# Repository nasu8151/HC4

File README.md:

¡¡¡ガバガバEnglish注意報発令中!!!

# Table of Contents
- [Table of Contents](#table-of-contents)
- [Descriptions](#descriptions)
- [Architecture](#architecture)
  - [Overview](#overview)
  - [Block diagram](#block-diagram)
  - [Instructions list](#instructions-list)
- [Software](#software)
- [List of files and folders](#list-of-files-and-folders)

# Descriptions

A 4- or 8-bit CPU made with 74-series logic ICs.

# Manuals

- Hardware manual (JP): [UsersManual_Hardware.md](./UsersManual_Hardware.md)
- Software manual (EN): [UsersManual_Software.md](./UsersManual_Software.md)
- Software manual (JP): [UsersManual_Software_JP.md](./UsersManual_Software_JP.md)

Document roles:

- Hardware manual (JP): block-level architecture, buses, control signals, model differences.
- Software manual (EN/JP): instruction set reference, programming caveats, and LED blink tutorial.

# Architecture
## Overview

HC4 has an 8-bit wide address bus and a 4-bit wide data bus.
All of instructions are 8-bit wide.

## Block diagram

## Instructions list

Please refer to [here](https://github.com/nasu8151/HC4/blob/main/UsersManual_Software.md).

## Schematics and Boards

If you don't have [KiCAD](https://www.kicad.org/), you can use KiCanvas to see our schematics and boards.
* [HC4](https://kicanvas.org/?repo=https%3A%2F%2Fgithub.com%2Fnasu8151%2FHC4%2Ftree%2Fmain%2FHC4_KiCad)
* [HC4<sub>E</sub>](https://kicanvas.org/?repo=https%3A%2F%2Fgithub.com%2Fnasu8151%2FHC4%2Ftree%2Fmain%2FHC4_KiCad_EE)

# Software

## Assembler

The assembler for this CPU can be found [here](https://github.com/nasu8151/hcxasm).
Please see the documents for syntax and other details.

## HC4eROMandRAM

This is a ROM/RAM emulator for HC4<sub>E</sub>.

# List of files and folders

<pre>
.
├─extra
├─HC4eROMandRAM
│  └─inst
├─hc4_asm
│  └─src
│      └─debug_data
├─HC4_KiCad
│  ├─HC4_gbr
│  ├─Library.pretty
│  └─sim
├─HC4_KiCad_EE
│  ├─HC4_KiCad_EE-backups
│  ├─Library.pretty
│  └─production
├─HC_MemoryBoard
│  ├─production
│  └─ThroughHole.pretty
└─verilog
    ├─HC4
    ├─HC4e
    └─HC8
</pre>

* [README.md](https://github.com/nasu8151/HC4) : This file.
* [UsersManual_Software.md](https://github.com/nasu8151/HC4/blob/main/UsersManual_Software.md) : Instruction manual.
* [hc4_asm/](https://github.com/nasu8151/HC4/blob/main/hc4_asm) : [DEPRECATED] : [Use new assembler](https://github.com/nasu8151/hcxasm). An assembler for the HC4 CPU.
* [HC4_KiCad](https://github.com/nasu8151/HC4/blob/main/HC4_KiCad) : Schematics and a board of the HC4.
* [HC4_KiCad_EE](https://github.com/nasu8151/HC4/blob/main/HC4_KiCad_EE) : Schematics and a board of the HC4<sub>E</sub> (Used to be called "HC4 Education Edition").
* [HC_MemoryBoard](https://github.com/nasu8151/HC4/blob/main/HC4_KiCad_EE) : A schematic and a board for SRAM and I/O.
* verilog/
  * [verilog/HC4](https://github.com/nasu8151/HC4/blob/main/verilog/HC4) : Verilog simulation files of the HC4 CPU.
  * [verilog/HC8](https://github.com/nasu8151/blob/main/HC4/verilog/HC8) : Verilog simulation files of the HC8 CPU.
  * [verilog/HC4e](https://github.com/nasu8151/blob/main/HC4/verilog/HC8) : Verilog simulation files of the HC4e CPU.

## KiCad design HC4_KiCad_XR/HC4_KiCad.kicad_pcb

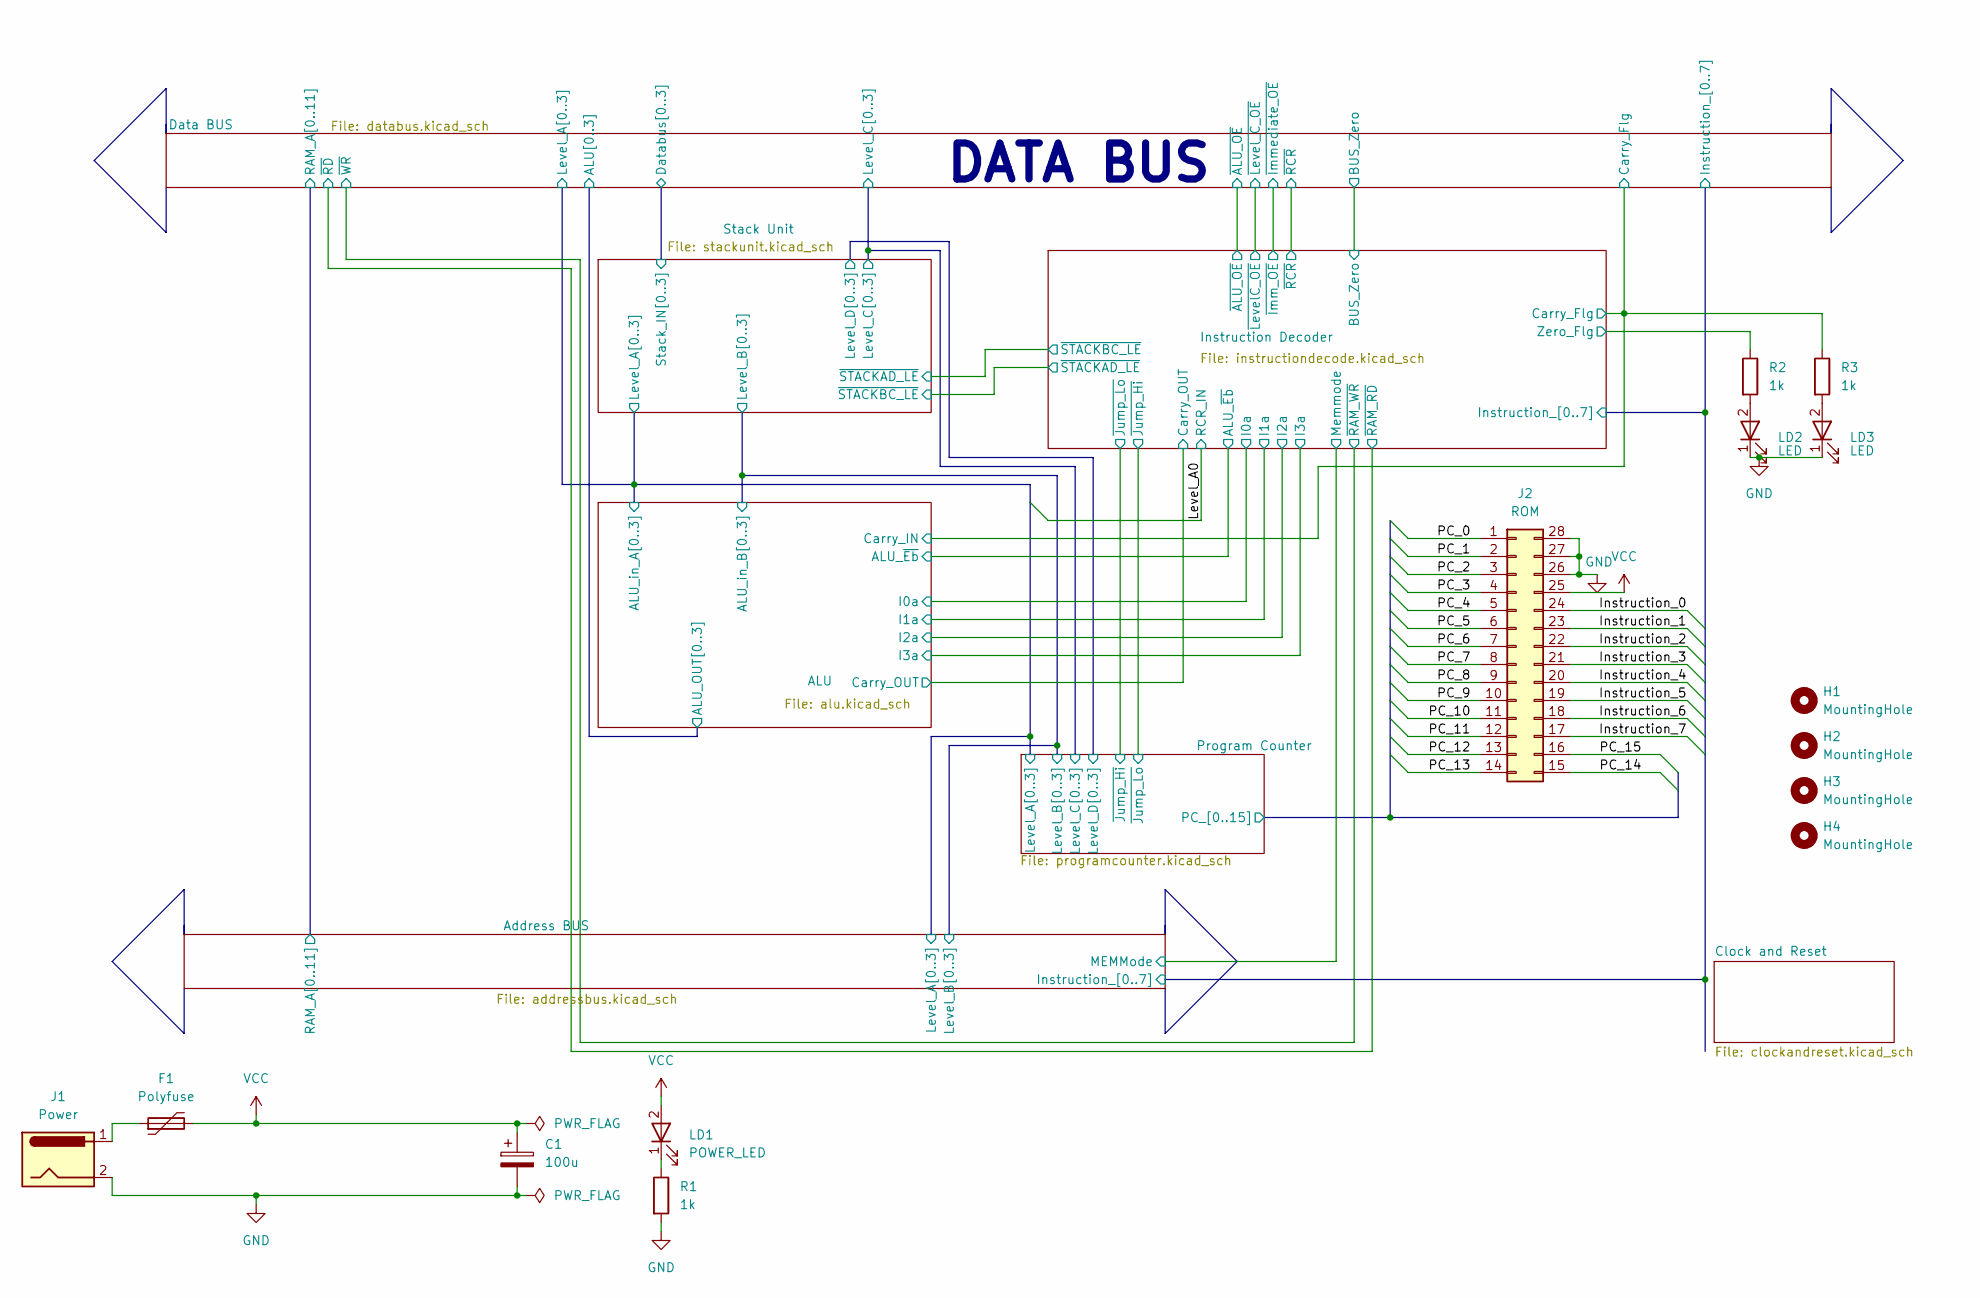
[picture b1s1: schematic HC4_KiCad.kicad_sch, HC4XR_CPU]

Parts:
C1: 100u; CP_Radial_D5.0mm_P2.50mm
F1: Polyfuse; Fuse_Bourns_MF-RG400
H1, H2, H3, H4: MountingHole; MountingHole_3.2mm_M3
J1: Power; BarrelJack_GCT_DCJ200-10-A_Horizontal
J2: ROM; PinHeader_2x14_P2.54mm_Vertical
LD1: POWER_LED; LED_Rectangular_W5.0mm_H2.0mm
LD2, LD3: LED; LED_Rectangular_W5.0mm_H2.0mm
R1, R2, R3: 1k; R_0603_1608Metric

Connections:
/Address BUS/Instruction_0: J2.24; also elsewhere on the board
/Address BUS/Instruction_1: J2.23; also elsewhere on the board
/Address BUS/Instruction_2: J2.22; also elsewhere on the board
/Address BUS/Instruction_3: J2.21; also elsewhere on the board
/Address BUS/Instruction_4: J2.20; also elsewhere on the board
/Address BUS/Instruction_5: J2.19; also elsewhere on the board
/Address BUS/Instruction_6: J2.18; also elsewhere on the board
/Address BUS/Instruction_7: J2.17; also elsewhere on the board
/Instruction Decoder/Carry_Flg: R3.1; also elsewhere on the board
/Instruction Decoder/Zero_Flg: R2.1; also elsewhere on the board
/Program Counter/PC_0: J2.1; also elsewhere on the board
/Program Counter/PC_1: J2.2; also elsewhere on the board
/Program Counter/PC_2: J2.3; also elsewhere on the board
/Program Counter/PC_3: J2.4; also elsewhere on the board
/Program Counter/PC_4: J2.5; also elsewhere on the board
/Program Counter/PC_5: J2.6; also elsewhere on the board
/Program Counter/PC_6: J2.7; also elsewhere on the board
/Program Counter/PC_7: J2.8; also elsewhere on the board
/Program Counter/PC_8: J2.9; also elsewhere on the board
/Program Counter/PC_9: J2.10; also elsewhere on the board
/Program Counter/PC_10: J2.11; also elsewhere on the board
/Program Counter/PC_11: J2.12; also elsewhere on the board
/Program Counter/PC_12: J2.13; also elsewhere on the board
/Program Counter/PC_13: J2.14; also elsewhere on the board
/Program Counter/PC_14: J2.15; also elsewhere on the board
/Program Counter/PC_15: J2.16; also elsewhere on the board
GND: C1.2, J1.2, J2.26, J2.27, J2.28, LD2.1 (K_1), LD3.1 (K_1), R1.2; also elsewhere on the board
unnamed: F1.1, J1.1
unnamed: LD1.1 (K_1), R1.1
unnamed: LD2.2, R2.2
unnamed: LD3.2, R3.2
VCC: C1.1, F1.2, J2.25, LD1.2; also elsewhere on the board

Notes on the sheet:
DATA BUS

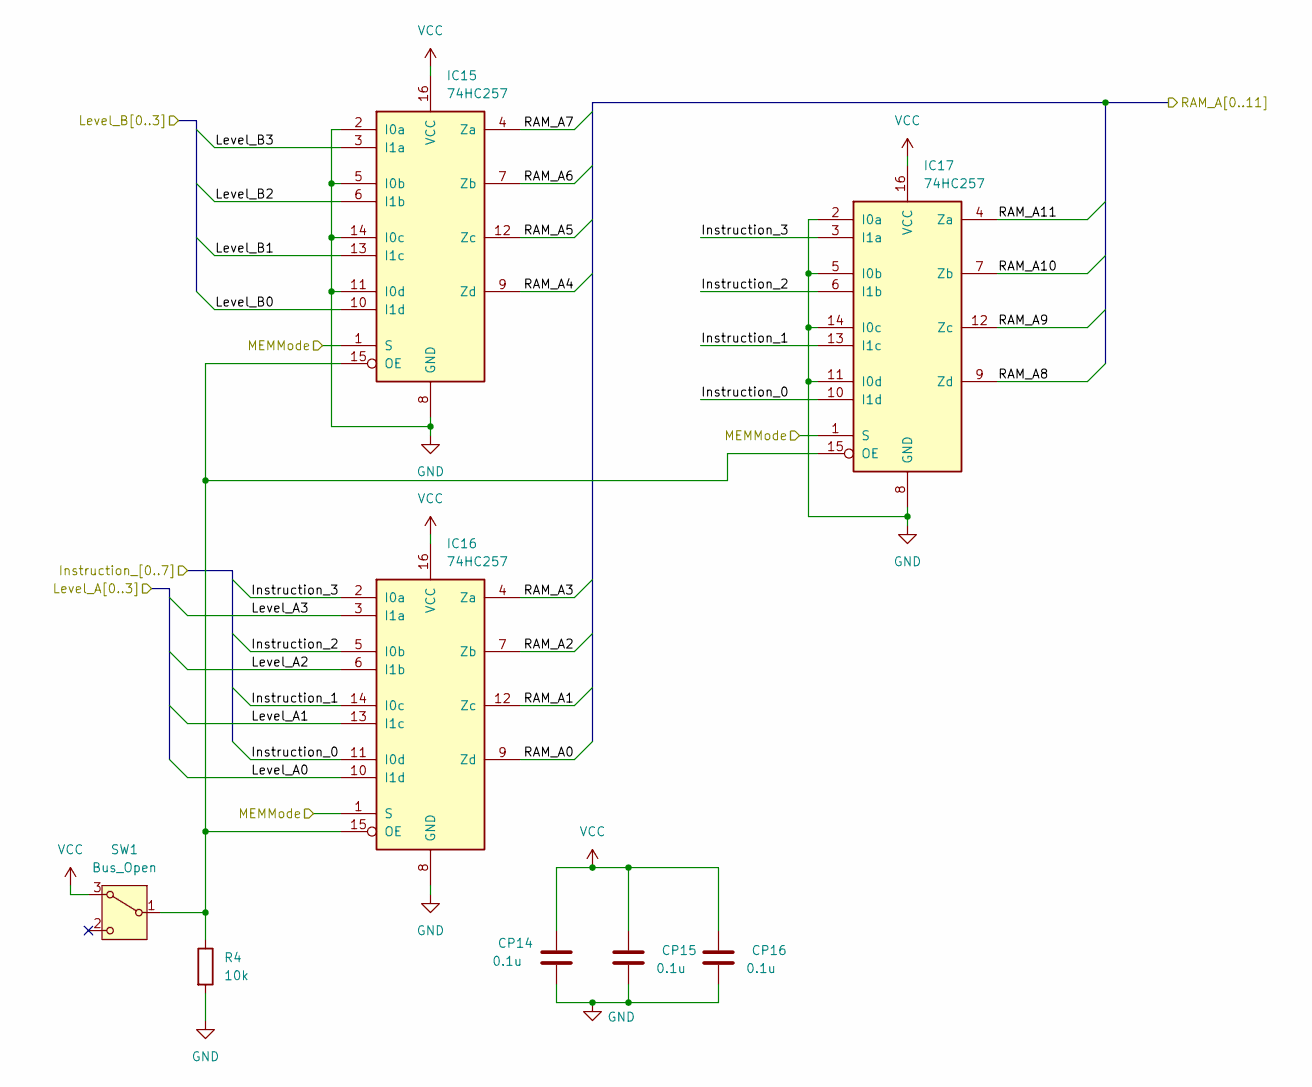
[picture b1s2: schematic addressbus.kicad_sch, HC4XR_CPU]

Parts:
CP14, CP15, CP16: 0.1u; C_0603_1608Metric
IC15, IC16, IC17: 74HC257; DIP-16_W7.62mm
R4: 10k; R_0603_1608Metric
SW1: Bus_Open; SW_Slide-03_Wuerth-WS-SLTV_10x2.5x6.4_P2.54mm

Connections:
/ALU/ALU_in_A0: IC16.10 (I1d); also elsewhere on the board
/ALU/ALU_in_A1: IC16.13 (I1c); also elsewhere on the board
/ALU/ALU_in_A2: IC16.6 (I1b); also elsewhere on the board
/ALU/ALU_in_A3: IC16.3 (I1a); also elsewhere on the board
/ALU/ALU_in_B0: IC15.10 (I1d); also elsewhere on the board
/ALU/ALU_in_B1: IC15.13 (I1c); also elsewhere on the board
/ALU/ALU_in_B2: IC15.6 (I1b); also elsewhere on the board
/ALU/ALU_in_B3: IC15.3 (I1a); also elsewhere on the board
/Address BUS/Instruction_0: IC16.11 (I0d), IC17.10 (I1d); also elsewhere on the board
/Address BUS/Instruction_1: IC16.14 (I0c), IC17.13 (I1c); also elsewhere on the board
/Address BUS/Instruction_2: IC16.5 (I0b), IC17.6 (I1b); also elsewhere on the board
/Address BUS/Instruction_3: IC16.2 (I0a), IC17.3 (I1a); also elsewhere on the board
/Address BUS/MEMMode: IC15.1 (S), IC16.1 (S), IC17.1 (S); also elsewhere on the board
/Address BUS/RAM_A0: IC16.9 (Zd); also elsewhere on the board
/Address BUS/RAM_A1: IC16.12 (Zc); also elsewhere on the board
/Address BUS/RAM_A2: IC16.7 (Zb); also elsewhere on the board
/Address BUS/RAM_A3: IC16.4 (Za); also elsewhere on the board
/Address BUS/RAM_A4: IC15.9 (Zd); also elsewhere on the board
/Address BUS/RAM_A5: IC15.12 (Zc); also elsewhere on the board
/Address BUS/RAM_A6: IC15.7 (Zb); also elsewhere on the board
/Address BUS/RAM_A7: IC15.4 (Za); also elsewhere on the board
/Address BUS/RAM_A8: IC17.9 (Zd); also elsewhere on the board
/Address BUS/RAM_A9: IC17.12 (Zc); also elsewhere on the board
/Address BUS/RAM_A10: IC17.7 (Zb); also elsewhere on the board
/Address BUS/RAM_A11: IC17.4 (Za); also elsewhere on the board
GND: CP14.2, CP15.2, CP16.2, IC15.2 (I0a), IC15.5 (I0b), IC15.8 (GND), IC15.11 (I0d), IC15.14 (I0c), IC16.8 (GND), IC17.2 (I0a), IC17.5 (I0b), IC17.8 (GND), IC17.11 (I0d), IC17.14 (I0c), R4.2; also elsewhere on the board
unnamed: IC15.15 (OE), IC16.15 (OE), IC17.15 (OE), R4.1, SW1.1 (B)
VCC: CP14.1, CP15.1, CP16.1, IC15.16 (VCC), IC16.16 (VCC), IC17.16 (VCC), SW1.3 (A); also elsewhere on the board

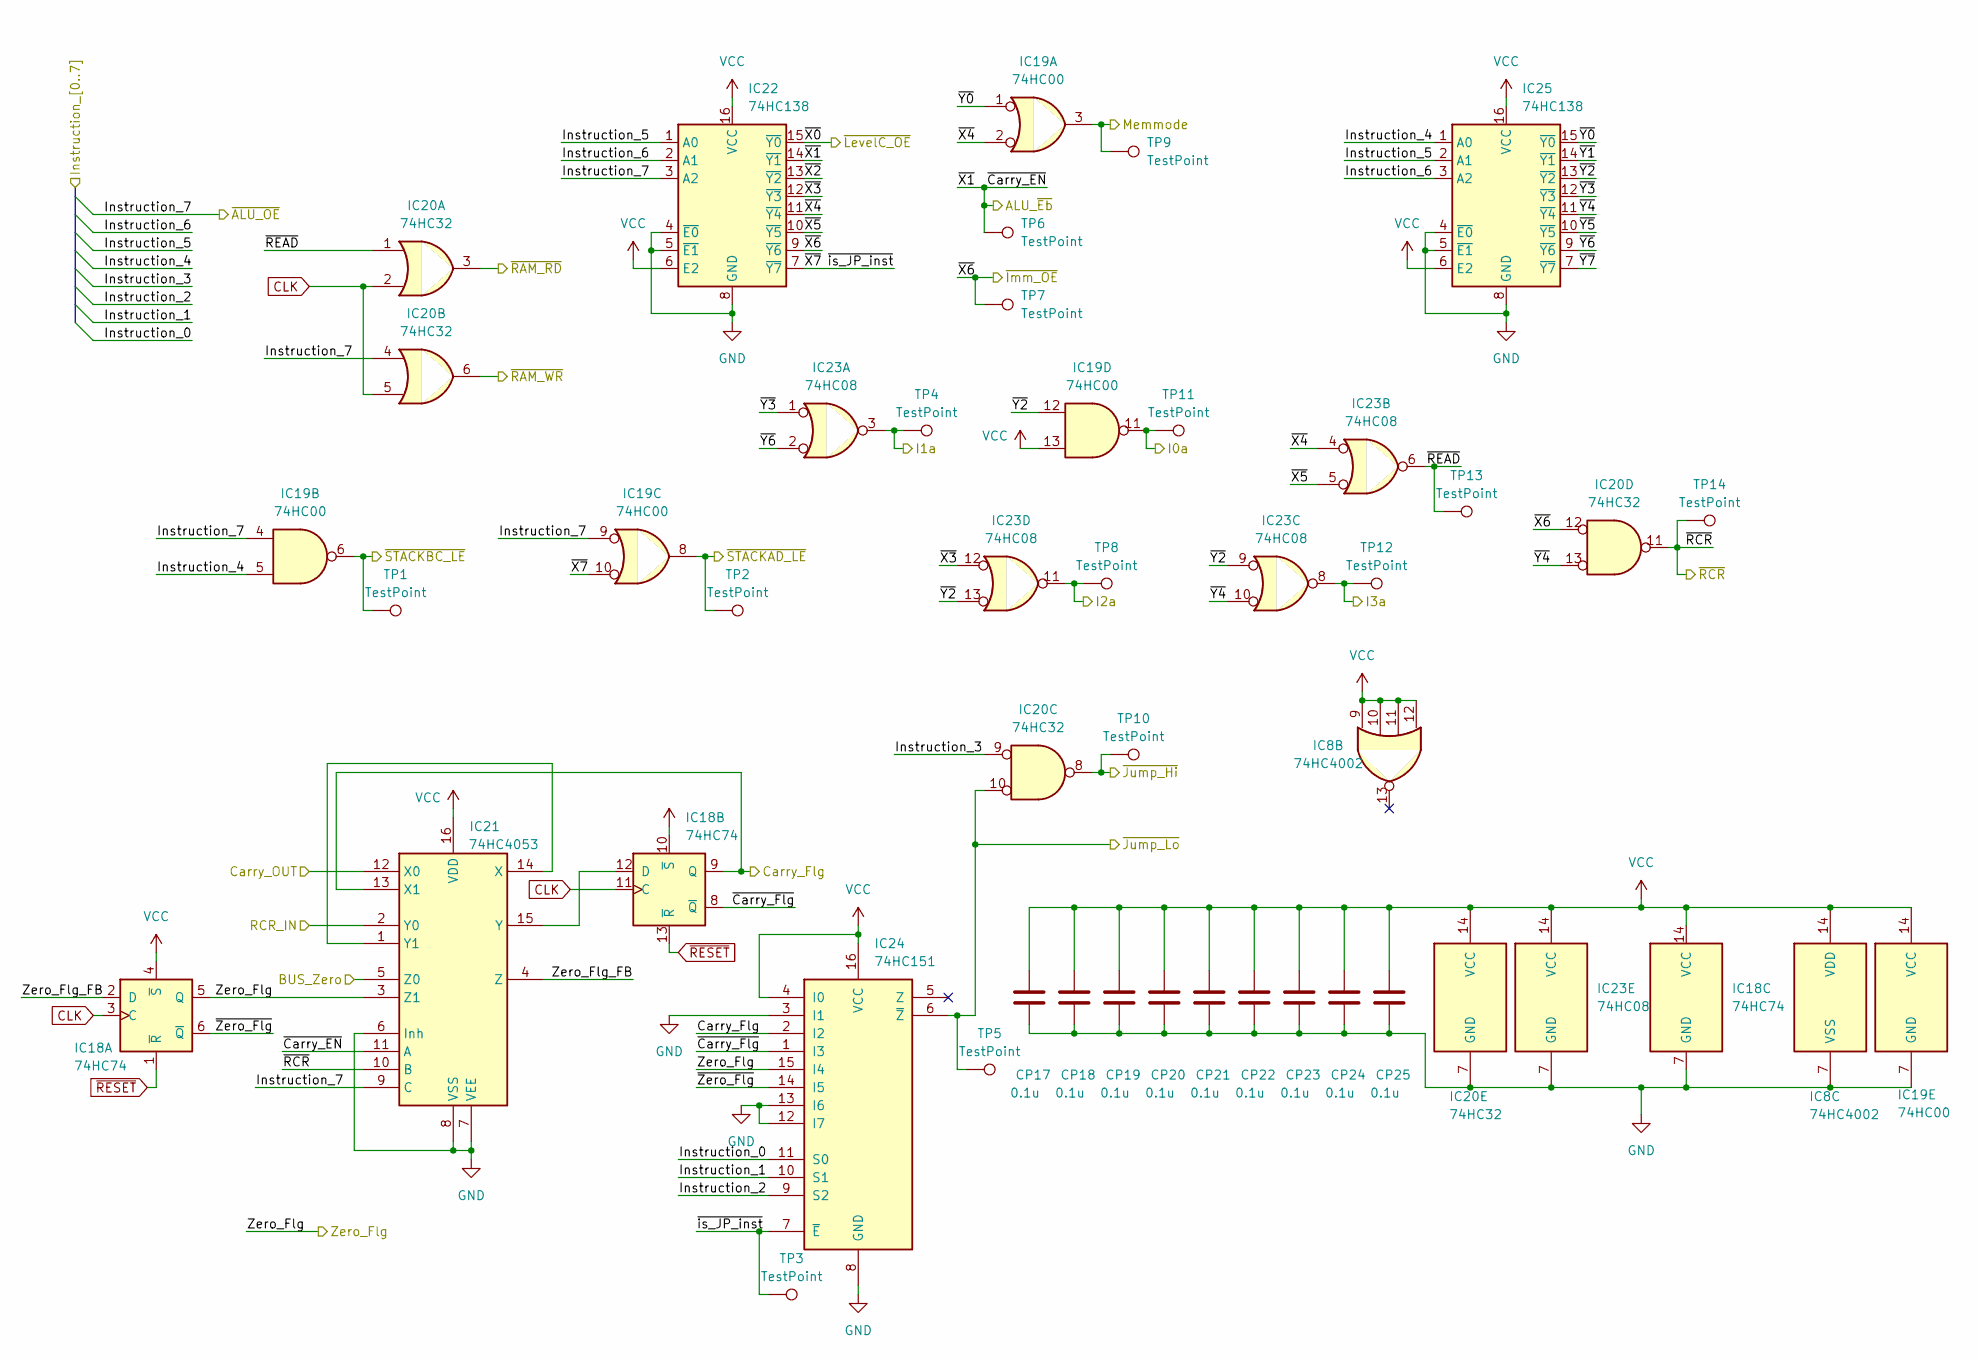
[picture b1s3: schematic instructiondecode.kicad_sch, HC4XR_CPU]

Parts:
CP17, CP18, CP19, CP20, CP21, CP22, CP23, CP24, CP25: 0.1u; C_0603_1608Metric
IC8: 74HC4002; DIP-14_W7.62mm
IC18: 74HC74; DIP-14_W7.62mm
IC19: 74HC00; DIP-14_W7.62mm
IC20: 74HC32; DIP-14_W7.62mm
IC21: 74HC4053; DIP-16_W7.62mm
IC22, IC25: 74HC138; DIP-16_W7.62mm
IC23: 74HC08; DIP-14_W7.62mm
IC24: 74HC151; DIP-16_W7.62mm
TP1, TP2, TP3, TP4, TP5, TP6, TP7, TP8, TP9, TP10, TP11, TP12, TP13, TP14: TestPoint; TestPoint_THTPad_1.0x1.0mm_Drill0.5mm

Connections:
/ALU/ALU_in_A0: IC21.2 (Y0); also elsewhere on the board
/ALU/Carry_OUT: IC21.12 (X0); also elsewhere on the board
/ALU/I0a: IC19.11, TP11.1 (1_1); also elsewhere on the board
/ALU/I1a: IC23.3, TP4.1 (1_1); also elsewhere on the board
/ALU/I2a: IC23.11, TP8.1 (1_1); also elsewhere on the board
/ALU/I3a: IC23.8, TP12.1 (1_1); also elsewhere on the board
/Address BUS/Instruction_0: IC24.11 (S0); also elsewhere on the board
/Address BUS/Instruction_1: IC24.10 (S1); also elsewhere on the board
/Address BUS/Instruction_2: IC24.9 (S2); also elsewhere on the board
/Address BUS/Instruction_3: IC20.9; also elsewhere on the board
/Address BUS/Instruction_4: IC19.5, IC25.1 (A0); also elsewhere on the board
/Address BUS/Instruction_5: IC22.1 (A0), IC25.2 (A1); also elsewhere on the board
/Address BUS/Instruction_6: IC22.2 (A1), IC25.3 (A2); also elsewhere on the board
/Address BUS/Instruction_7: IC19.4, IC19.9, IC20.4, IC21.9 (C), IC22.3 (A2); also elsewhere on the board
/Address BUS/MEMMode: IC19.3, TP9.1 (1_1); also elsewhere on the board
/Data BUS/BUS_Zero: IC8.1, IC21.5 (Z0)
/Data BUS/Databus0: IC8.5; also elsewhere on the board
/Data BUS/Databus1: IC8.4; also elsewhere on the board
/Data BUS/Databus2: IC8.3; also elsewhere on the board
/Data BUS/Databus3: IC8.2; also elsewhere on the board
/Data BUS/~RD: IC20.3; also elsewhere on the board
/Data BUS/~WR: IC20.6; also elsewhere on the board
/Instruction Decoder/Carry_Flg: IC18.9 (Q), IC21.13 (X1), IC24.2 (I2); also elsewhere on the board
/Instruction Decoder/Zero_Flg: IC18.5 (Q), IC21.3 (Z1), IC24.15 (I4); also elsewhere on the board
/Instruction Decoder/Zero_Flg_FB: IC18.2 (D), IC21.4 (Z)
/Instruction Decoder/~Carry_EN: IC21.11 (A), IC22.14 (~Y1), TP6.1 (1_1); also elsewhere on the board
/Instruction Decoder/~Carry_Flg: IC18.8 (~Q), IC24.1 (I3)
/Instruction Decoder/~Jump_Hi: IC20.8, TP10.1 (1_1); also elsewhere on the board
/Instruction Decoder/~Jump_Lo: IC20.10, IC24.6 (~Z), TP5.1 (1_1); also elsewhere on the board
/Instruction Decoder/~RCR: IC20.11, IC21.10 (B), TP14.1 (1_1); also elsewhere on the board
/Instruction Decoder/~READ: IC20.1, IC23.6, TP13.1 (1_1)
/Instruction Decoder/~STACKAD_LE: IC19.8, TP2.1 (1_1); also elsewhere on the board
/Instruction Decoder/~STACKBC_LE: IC19.6, TP1.1 (1_1); also elsewhere on the board
/Instruction Decoder/~X0: IC22.15 (~Y0); also elsewhere on the board
/Instruction Decoder/~X2: IC22.13 (~Y2)
/Instruction Decoder/~X3: IC22.12 (~Y3), IC23.12
/Instruction Decoder/~X4: IC19.2, IC22.11 (~Y4), IC23.4
/Instruction Decoder/~X5: IC22.10 (~Y5), IC23.5
/Instruction Decoder/~X6: IC20.12, IC22.9 (~Y6), TP7.1 (1_1); also elsewhere on the board
/Instruction Decoder/~X7: IC19.10, IC22.7 (~Y7), IC24.7 (~E), TP3.1 (1_1)
/Instruction Decoder/~Y0: IC19.1, IC25.15 (~Y0)
/Instruction Decoder/~Y1: IC25.14 (~Y1)
/Instruction Decoder/~Y2: IC19.12, IC23.9, IC23.13, IC25.13 (~Y2)
/Instruction Decoder/~Y3: IC23.1, IC25.12 (~Y3)
/Instruction Decoder/~Y4: IC20.13, IC23.10, IC25.11 (~Y4)
/Instruction Decoder/~Y5: IC25.10 (~Y5)
/Instruction Decoder/~Y6: IC23.2, IC25.9 (~Y6)
/Instruction Decoder/~Y7: IC25.7 (~Y7)
/Instruction Decoder/~Zero_Flg: IC18.6 (~Q), IC24.14 (I5)
CLK: IC18.3 (C), IC18.11 (C), IC20.2, IC20.5; also elsewhere on the board
GND: CP17.2, CP18.2, CP19.2, CP20.2, CP21.2, CP22.2, CP23.2, CP24.2, CP25.2, IC8.7 (VSS), IC18.7 (GND), IC19.7 (GND), IC20.7 (GND), IC21.6 (Inh), IC21.7 (VEE), IC21.8 (VSS), IC22.4 (~E0), IC22.5 (~E1), IC22.8 (GND), IC23.7 (GND), IC24.3 (I1), IC24.8 (GND), IC24.12 (I7), IC24.13 (I6), IC25.4 (~E0), IC25.5 (~E1), IC25.8 (GND); also elsewhere on the board
unnamed: IC18.12 (D), IC21.15 (Y)
unnamed: IC21.1 (Y1), IC21.14 (X)
VCC: CP17.1, CP18.1, CP19.1, CP20.1, CP21.1, CP22.1, CP23.1, CP24.1, CP25.1, IC8.9, IC8.10, IC8.11, IC8.12, IC8.14 (VDD), IC18.4 (~S), IC18.10 (~S), IC18.14 (VCC), IC19.13, IC19.14 (VCC), IC20.14 (VCC), IC21.16 (VDD), IC22.6 (E2), IC22.16 (VCC), IC23.14 (VCC), IC24.4 (I0), IC24.16 (VCC), IC25.6 (E2), IC25.16 (VCC); also elsewhere on the board
~RESET: IC18.1 (~R), IC18.13 (~R); also elsewhere on the board

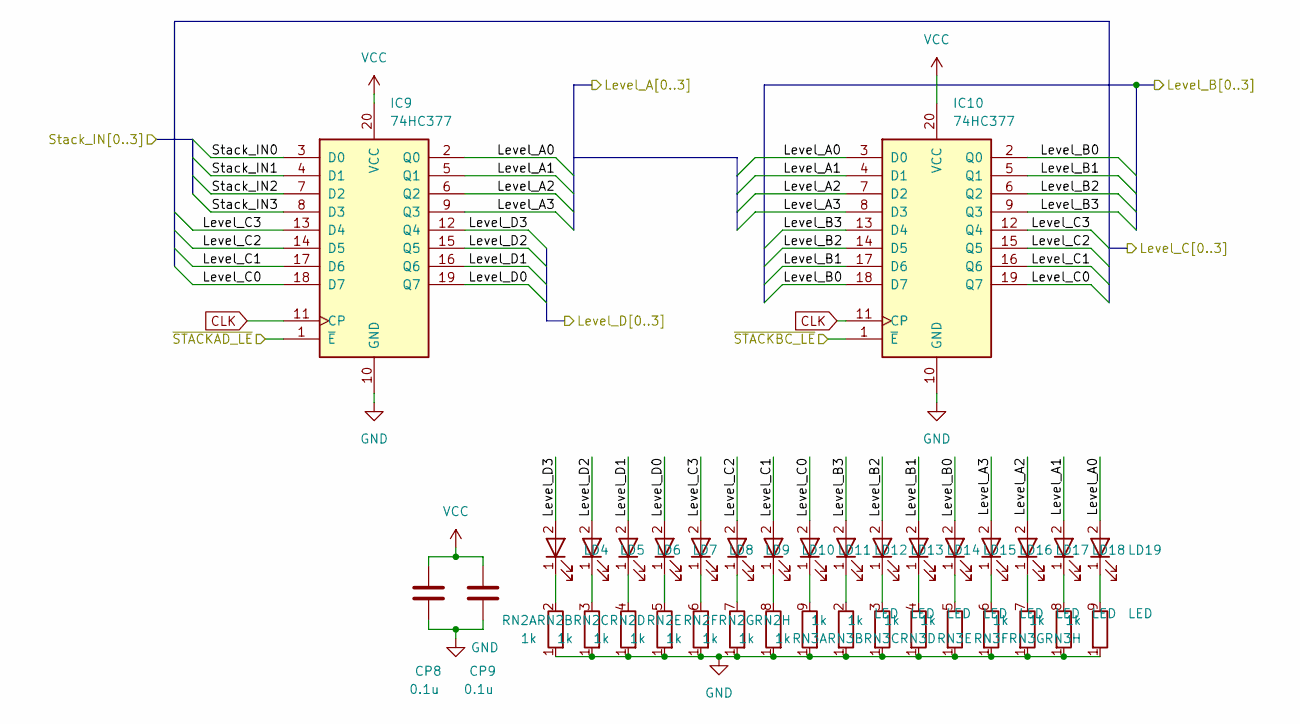
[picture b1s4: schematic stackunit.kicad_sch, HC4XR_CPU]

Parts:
CP8, CP9: 0.1u; C_0603_1608Metric
IC9, IC10: 74HC377; DIP-20_W7.62mm
LD4, LD5, LD6, LD7, LD8, LD9, LD10, LD11, LD12, LD13, LD14, LD15, LD16, LD17, LD18, LD19: LED; LED_Rectangular_W5.0mm_H2.0mm
RN2, RN3: 1k; R_Array_SIP9

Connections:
/ALU/ALU_in_A0: IC9.2 (Q0), IC10.3 (D0), LD19.2; also elsewhere on the board
/ALU/ALU_in_A1: IC9.5 (Q1), IC10.4 (D1), LD18.2; also elsewhere on the board
/ALU/ALU_in_A2: IC9.6 (Q2), IC10.7 (D2), LD17.2; also elsewhere on the board
/ALU/ALU_in_A3: IC9.9 (Q3), IC10.8 (D3), LD16.2; also elsewhere on the board
/ALU/ALU_in_B0: IC10.2 (Q0), IC10.18 (D7), LD15.2; also elsewhere on the board
/ALU/ALU_in_B1: IC10.5 (Q1), IC10.17 (D6), LD14.2; also elsewhere on the board
/ALU/ALU_in_B2: IC10.6 (Q2), IC10.14 (D5), LD13.2; also elsewhere on the board
/ALU/ALU_in_B3: IC10.9 (Q3), IC10.13 (D4), LD12.2; also elsewhere on the board
/Data BUS/Databus0: IC9.3 (D0); also elsewhere on the board
/Data BUS/Databus1: IC9.4 (D1); also elsewhere on the board
/Data BUS/Databus2: IC9.7 (D2); also elsewhere on the board
/Data BUS/Databus3: IC9.8 (D3); also elsewhere on the board
/Data BUS/Level_C0: IC9.18 (D7), IC10.19 (Q7), LD11.2; also elsewhere on the board
/Data BUS/Level_C1: IC9.17 (D6), IC10.16 (Q6), LD10.2; also elsewhere on the board
/Data BUS/Level_C2: IC9.14 (D5), IC10.15 (Q5), LD9.2; also elsewhere on the board
/Data BUS/Level_C3: IC9.13 (D4), IC10.12 (Q4), LD8.2; also elsewhere on the board
/Instruction Decoder/~STACKAD_LE: IC10.1 (~E); also elsewhere on the board
/Instruction Decoder/~STACKBC_LE: IC9.1 (~E); also elsewhere on the board
/Program Counter/Level_D0: IC9.19 (Q7), LD7.2; also elsewhere on the board
/Program Counter/Level_D1: IC9.16 (Q6), LD6.2; also elsewhere on the board
/Program Counter/Level_D2: IC9.15 (Q5), LD5.2; also elsewhere on the board
/Program Counter/Level_D3: IC9.12 (Q4), LD4.2; also elsewhere on the board
CLK: IC9.11 (CP), IC10.11 (CP); also elsewhere on the board
GND: CP8.2, CP9.2, IC9.10 (GND), IC10.10 (GND), RN2.1 (R1), RN3.1 (R1); also elsewhere on the board
unnamed: LD4.1 (K_1), RN2.2 (R1.2)
unnamed: LD5.1 (K_1), RN2.3 (R2.2)
unnamed: LD6.1 (K_1), RN2.4 (R3.2)
unnamed: LD7.1 (K_1), RN2.5 (R4.2)
unnamed: LD8.1 (K_1), RN2.6 (R5.2)
unnamed: LD9.1 (K_1), RN2.7 (R6.2)
unnamed: LD10.1 (K_1), RN2.8 (R7.2)
unnamed: LD11.1 (K_1), RN2.9 (R8.2)
unnamed: LD12.1 (K_1), RN3.2 (R1.2)
unnamed: LD13.1 (K_1), RN3.3 (R2.2)
unnamed: LD14.1 (K_1), RN3.4 (R3.2)
unnamed: LD15.1 (K_1), RN3.5 (R4.2)
unnamed: LD16.1 (K_1), RN3.6 (R5.2)
unnamed: LD17.1 (K_1), RN3.7 (R6.2)
unnamed: LD18.1 (K_1), RN3.8 (R7.2)
unnamed: LD19.1 (K_1), RN3.9 (R8.2)
VCC: CP8.1, CP9.1, IC9.20 (VCC), IC10.20 (VCC); also elsewhere on the board

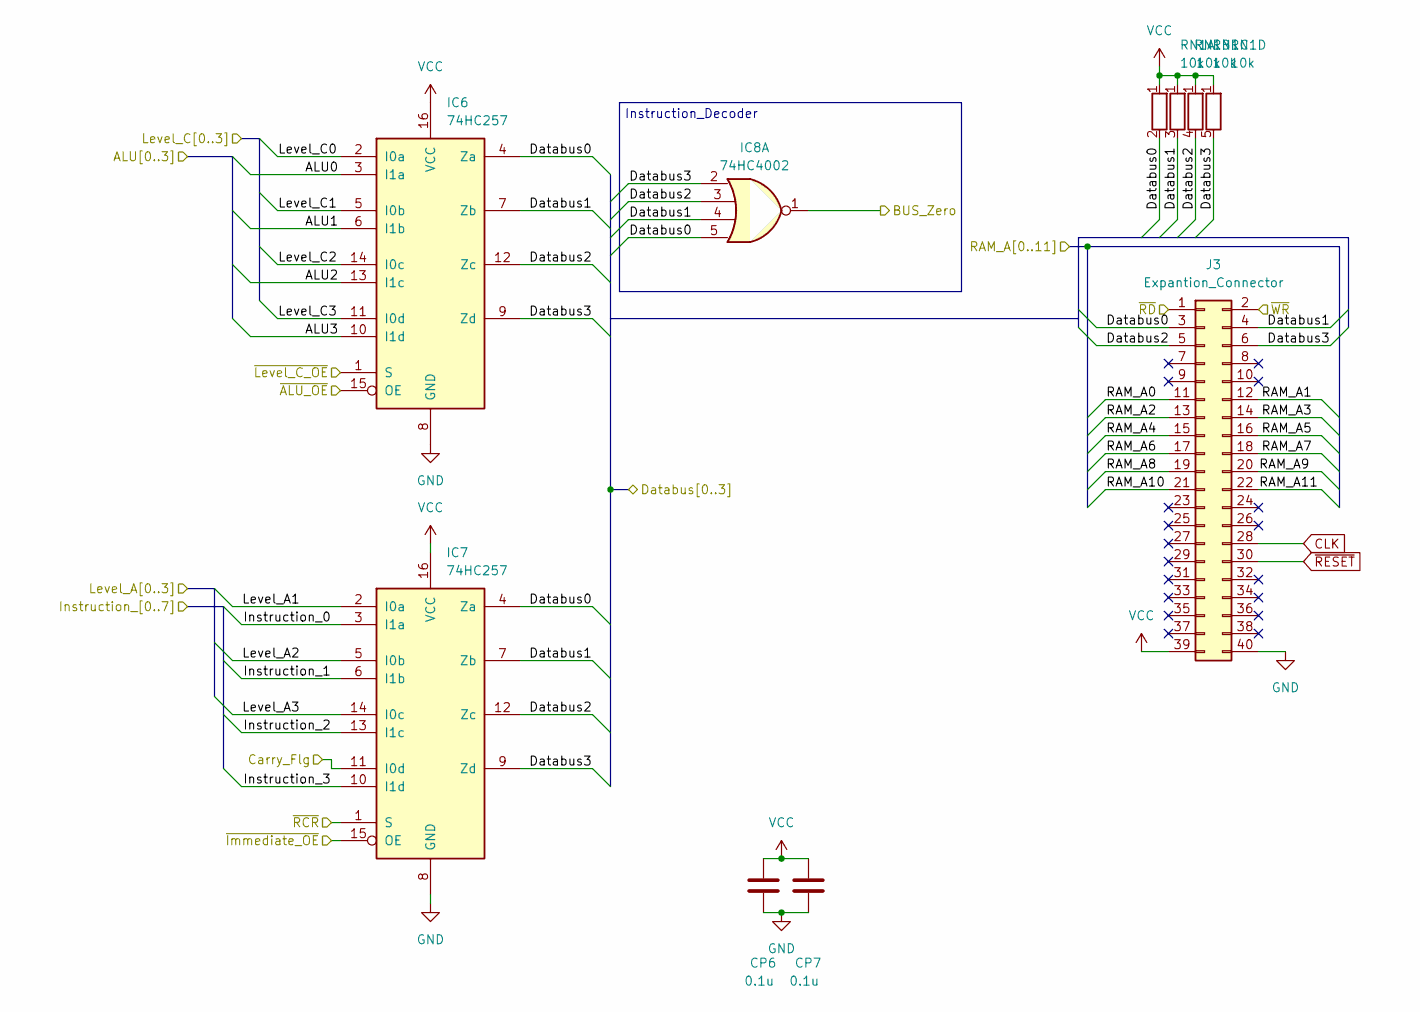
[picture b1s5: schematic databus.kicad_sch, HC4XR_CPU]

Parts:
CP6, CP7: 0.1u; C_0603_1608Metric
IC6, IC7: 74HC257; DIP-16_W7.62mm
IC8: 74HC4002; DIP-14_W7.62mm
J3: Expantion_Connector; PinHeader_2x20_P2.54mm_Vertical
RN1: 10k; R_Array_SIP5

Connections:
/ALU/ALU_OUT0: IC6.3 (I1a); also elsewhere on the board
/ALU/ALU_OUT1: IC6.6 (I1b); also elsewhere on the board
/ALU/ALU_OUT2: IC6.13 (I1c); also elsewhere on the board
/ALU/ALU_OUT3: IC6.10 (I1d); also elsewhere on the board
/ALU/ALU_in_A1: IC7.2 (I0a); also elsewhere on the board
/ALU/ALU_in_A2: IC7.5 (I0b); also elsewhere on the board
/ALU/ALU_in_A3: IC7.14 (I0c); also elsewhere on the board
/Address BUS/Instruction_0: IC7.3 (I1a); also elsewhere on the board
/Address BUS/Instruction_1: IC7.6 (I1b); also elsewhere on the board
/Address BUS/Instruction_2: IC7.13 (I1c); also elsewhere on the board
/Address BUS/Instruction_3: IC7.10 (I1d); also elsewhere on the board
/Address BUS/Instruction_7: IC6.15 (OE); also elsewhere on the board
/Address BUS/RAM_A0: J3.11; also elsewhere on the board
/Address BUS/RAM_A1: J3.12; also elsewhere on the board
/Address BUS/RAM_A2: J3.13; also elsewhere on the board
/Address BUS/RAM_A3: J3.14; also elsewhere on the board
/Address BUS/RAM_A4: J3.15; also elsewhere on the board
/Address BUS/RAM_A5: J3.16; also elsewhere on the board
/Address BUS/RAM_A6: J3.17; also elsewhere on the board
/Address BUS/RAM_A7: J3.18; also elsewhere on the board
/Address BUS/RAM_A8: J3.19; also elsewhere on the board
/Address BUS/RAM_A9: J3.20; also elsewhere on the board
/Address BUS/RAM_A10: J3.21; also elsewhere on the board
/Address BUS/RAM_A11: J3.22; also elsewhere on the board
/Data BUS/BUS_Zero: IC8.1; also elsewhere on the board
/Data BUS/Databus0: IC6.4 (Za), IC7.4 (Za), IC8.5, J3.3, RN1.2 (R1.2); also elsewhere on the board
/Data BUS/Databus1: IC6.7 (Zb), IC7.7 (Zb), IC8.4, J3.4, RN1.3 (R2.2); also elsewhere on the board
/Data BUS/Databus2: IC6.12 (Zc), IC7.12 (Zc), IC8.3, J3.5, RN1.4 (R3.2); also elsewhere on the board
/Data BUS/Databus3: IC6.9 (Zd), IC7.9 (Zd), IC8.2, J3.6, RN1.5 (R4.2); also elsewhere on the board
/Data BUS/Level_C0: IC6.2 (I0a); also elsewhere on the board
/Data BUS/Level_C1: IC6.5 (I0b); also elsewhere on the board
/Data BUS/Level_C2: IC6.14 (I0c); also elsewhere on the board
/Data BUS/Level_C3: IC6.11 (I0d); also elsewhere on the board
/Data BUS/~RD: J3.1; also elsewhere on the board
/Data BUS/~WR: J3.2; also elsewhere on the board
/Instruction Decoder/Carry_Flg: IC7.11 (I0d); also elsewhere on the board
/Instruction Decoder/~RCR: IC7.1 (S); also elsewhere on the board
/Instruction Decoder/~X0: IC6.1 (S); also elsewhere on the board
/Instruction Decoder/~X6: IC7.15 (OE); also elsewhere on the board
CLK: J3.28; also elsewhere on the board
GND: CP6.2, CP7.2, IC6.8 (GND), IC7.8 (GND), J3.40; also elsewhere on the board
VCC: CP6.1, CP7.1, IC6.16 (VCC), IC7.16 (VCC), J3.39, RN1.1 (R1); also elsewhere on the board
~RESET: J3.30; also elsewhere on the board

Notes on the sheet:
Instruction_Decoder

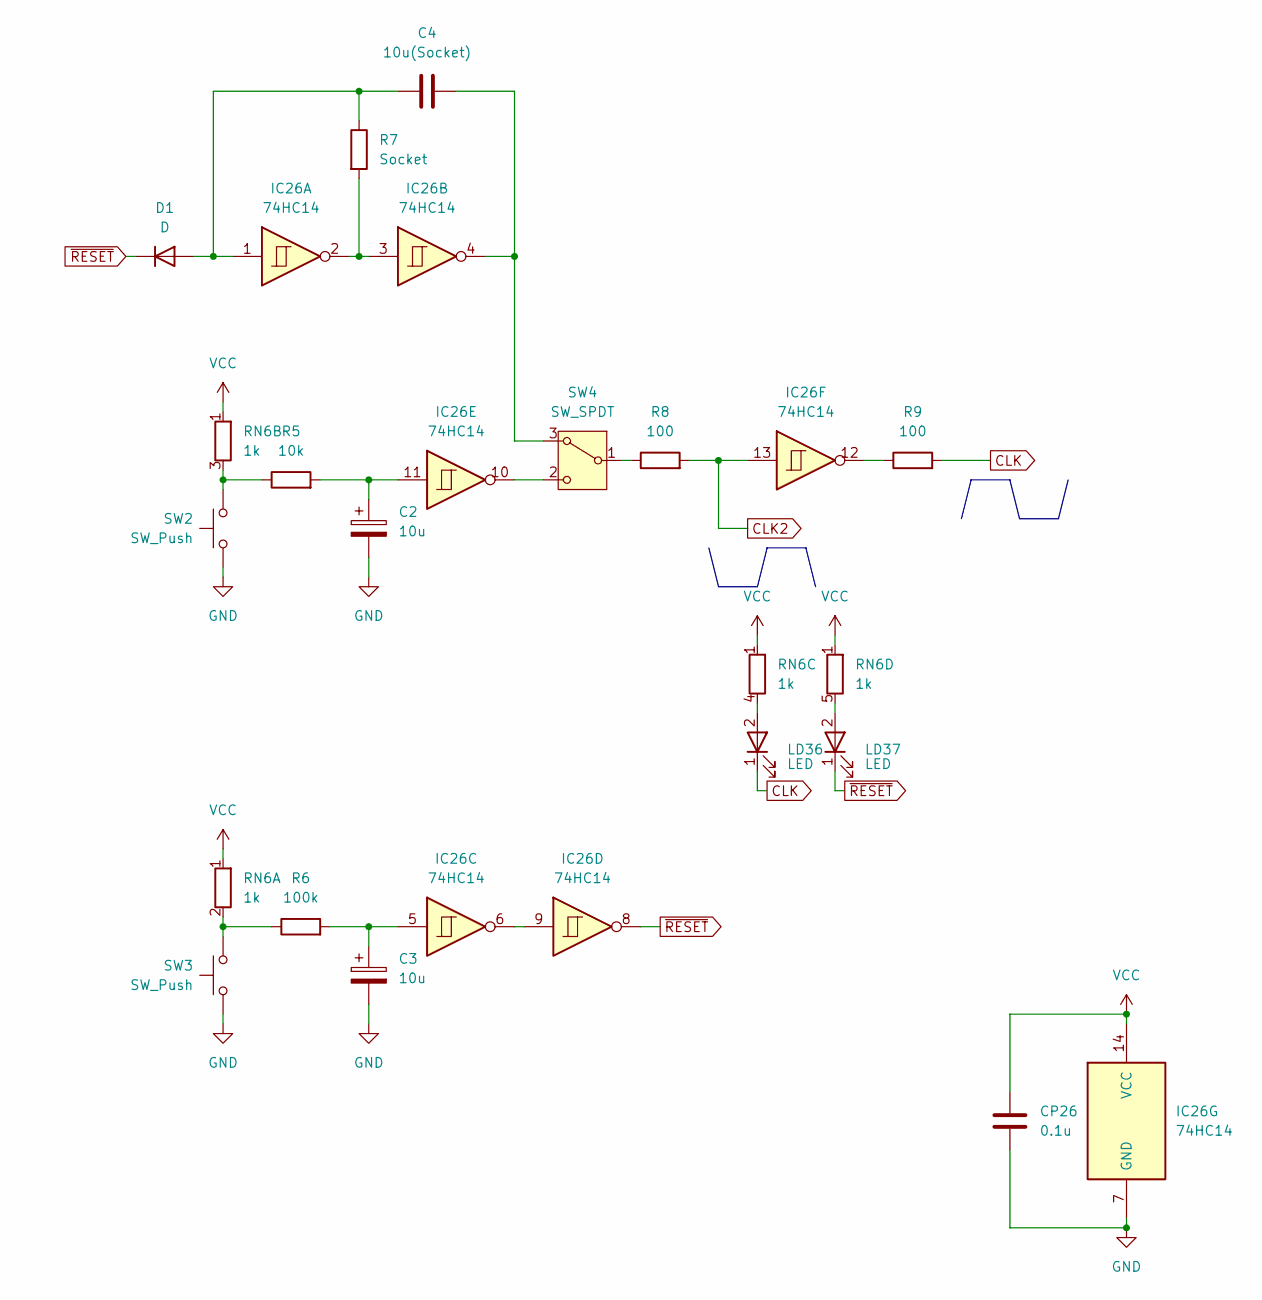
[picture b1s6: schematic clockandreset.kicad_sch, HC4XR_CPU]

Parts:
C2, C3: 10u; CP_Radial_D5.0mm_P2.50mm
C4: 10u(Socket); C_Radial_D6.3mm_H5.0mm_P2.50mm
CP26: 0.1u; C_0603_1608Metric
D1: D; D_SOD-523
IC26: 74HC14; DIP-14_W7.62mm
LD36, LD37: LED; LED_Rectangular_W5.0mm_H2.0mm
R5: 10k; R_0603_1608Metric
R6: 100k; R_0603_1608Metric
R7: Socket; R_Axial_DIN0207_L6.3mm_D2.5mm_P10.16mm_Horizontal
R8, R9: 100; R_0603_1608Metric
RN6: 1k; R_Array_SIP5
SW2, SW3: SW_Push; SW_PUSH_6mm
SW4: SW_SPDT; SW_Slide-03_Wuerth-WS-SLTV_10x2.5x6.4_P2.54mm

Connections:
CLK: LD36.1 (K_1), R9.2; also elsewhere on the board
CLK2: IC26.13, R8.2
GND: C2.2, C3.2, CP26.2, IC26.7 (GND), SW2.1, SW3.1; also elsewhere on the board
unnamed: C2.1, IC26.11, R5.2
unnamed: C3.1, IC26.5, R6.2
unnamed: C4.1, D1.2 (A), IC26.1, R7.1
unnamed: IC26.2, IC26.3, R7.2
unnamed: IC26.6, IC26.9
unnamed: IC26.12, R9.1
unnamed: R6.1, RN6.2 (R1.2), SW3.2
unnamed: R5.1, RN6.3 (R2.2), SW2.2
unnamed: LD36.2, RN6.4 (R3.2)
unnamed: LD37.2, RN6.5 (R4.2)
unnamed: C4.2, IC26.4, SW4.3 (A)
unnamed: R8.1, SW4.1 (B)
unnamed: IC26.10, SW4.2 (C)
VCC: CP26.1, IC26.14 (VCC), RN6.1 (R1); also elsewhere on the board
~RESET: D1.1 (K), IC26.8, LD37.1 (K_1); also elsewhere on the board

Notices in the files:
HC4_KiCad/HC4_KiCad.kicad_pcb:
(C)2025-26
HC4_KiCad_XR/HC4_KiCad.kicad_pcb:
(C)2025-26 DGK
